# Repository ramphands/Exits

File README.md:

# MOUTH

### ⚠️ THIS MODULE HAS NOT YET BEEN BUILT, ATTEMPT TO BUILD AT YOUR OWN RISK ⚠️

MOUTH is a DIY 8hp eurorack module designed to be the output stage of your patches. It has a 4 channel mixer with individual pan and level controls, and line and headphone outputs.

The project was derived from the [Exits](https://github.com/ramphands/Exits) module. Exits was a combination of the lines mixer project [Nearness](https://github.com/sarnesjo/nearness) and the [Forestcaver headphone amp](https://github.com/forestcaver/Analog-Voice/tree/master/AJH_Headphone_Amp). For MOUTH The patch-based stereo panning of Exits and nearness was changed out for individual pan and level controls for 4 tracks, and the Forestcaver headphone amp (based on the NJM4556AV-TE1 opamp) was changed out for a headphone amp loosely based on Chu Moy's famous ["CMoy" design](https://web.archive.org/web/20021223020724/http://headwize2.powerpill.org/projects/showproj.php?file=cmoy2_prj.htm) - in this case using the RC4580 instead of the OPA134 for availability and experimentation reasons. The module was expanded from 4hp to 8hp to accomodate the extra knobs. I also switched from 1/4" jacks for the two outputs - to 1/8" jacks for everything. The extra space on the widened input board, along with removing the two tall 1/4" jacks, allowed me to flatten the module from two PCBs to just one.

If you'd like to explore the pan + mix section, circuitjs simulation files are in the [simulations](simulations) directory.

The four mixer channels are DC coupled, so you can use this module to mix CV. The headphone output is not DC coupled, so only the line output will output DC offsets. At maximum volume the headphone output is about 1/10 the input level. J5 and J6 are jumpers - no pins bridged means the mixer has a gain of about 1x. Bridging pins 1 and 2 on both jumpers will set the mixer sections gain to 2/3x in case you're mixing hot signals and want to tone things down a bit. To add gain, you could bridge pins 1+2 and then desolder R17 and R20. That'll set the gain to just shy of 2x.

The following sources were used either directly or as learning material to construct the panning and mixing section:

- [Audio Signal Mixing](https://sound-au.com/articles/audio-mixing.htm) By Rod Elliott - a fantastic explainer of mixing circuits
- Erica Synths DIY eurorack [Output and Mixer](https://github.com/erica-synths/diy-eurorack) modules
- [Befaco Hexmix](http://www.befaco.org/hexmix/)

## Schematic and PCBs

-- CURRENTLY OUT OF DATE --

The [kicad](kicad) directory contains the schematic and PCB layout as a KiCad 6 project.

## Panel

-- CURRENTLY OUT OF DATE --

Available in the [panel](panel) directory as a PDF and an SVG vector file.

## Revisions and notes 

- Started with this commit of [Exits](https://github.com/ramphands/Exits/tree/e56ce6f3a76ff6dc0b776ba10d0bfae7fea7ace0)
- Switched from 4hp to 8hp
- Switched from 7 input channels to 4
- Switched from 1/4" jacks for line and hp to 3.5mm / 1/8" jacks for everything.
- Flattened the design from two PCBs to just PCB
- Switched to a CMOY style headphone output using the RC4580
- MOUTH's first "complete" post-Exits scheamtic, using passive mixing can be found in the git history [here](https://github.com/coryalder/Exits/blob/65a9d2693df2f5ae9116ffd591f22e5cf609d3db/exits%20schematic.april12th.pdf). After that I switched to current based mixing, per Rod Elliott's article
- MOUTH's first "complete" + "current-based" schematic is [here](https://github.com/coryalder/Exits/tree/e56ce6f3a76ff6dc0b776ba10d0bfae7fea7ace0)
- Re-routed the board with the changes above

## Todos:

- Make a panel and panel template
- Add 3d models for all the parts used
- Add board rendering images to the readme
- Add test points to make debugging easier
- Build one, and confirm all of this works as intended

## License

[CC BY-SA 4.0](http://creativecommons.org/licenses/by-sa/4.0/)

To summarize the license linked above - you are free to:

* Share — copy and redistribute the material in any medium or format
* Adapt — remix, transform, and build upon the material
for any purpose, even commercially. 

As long as you abide by the terms of the license which requires:

* Attribution — You must give appropriate credit, provide a link to the license, and indicate if changes were made. You may do so in any reasonable manner, but not in any way that suggests the licensor endorses you or your use.

* ShareAlike — If you remix, transform, or build upon the material, you must distribute your contributions under the same license as the original.

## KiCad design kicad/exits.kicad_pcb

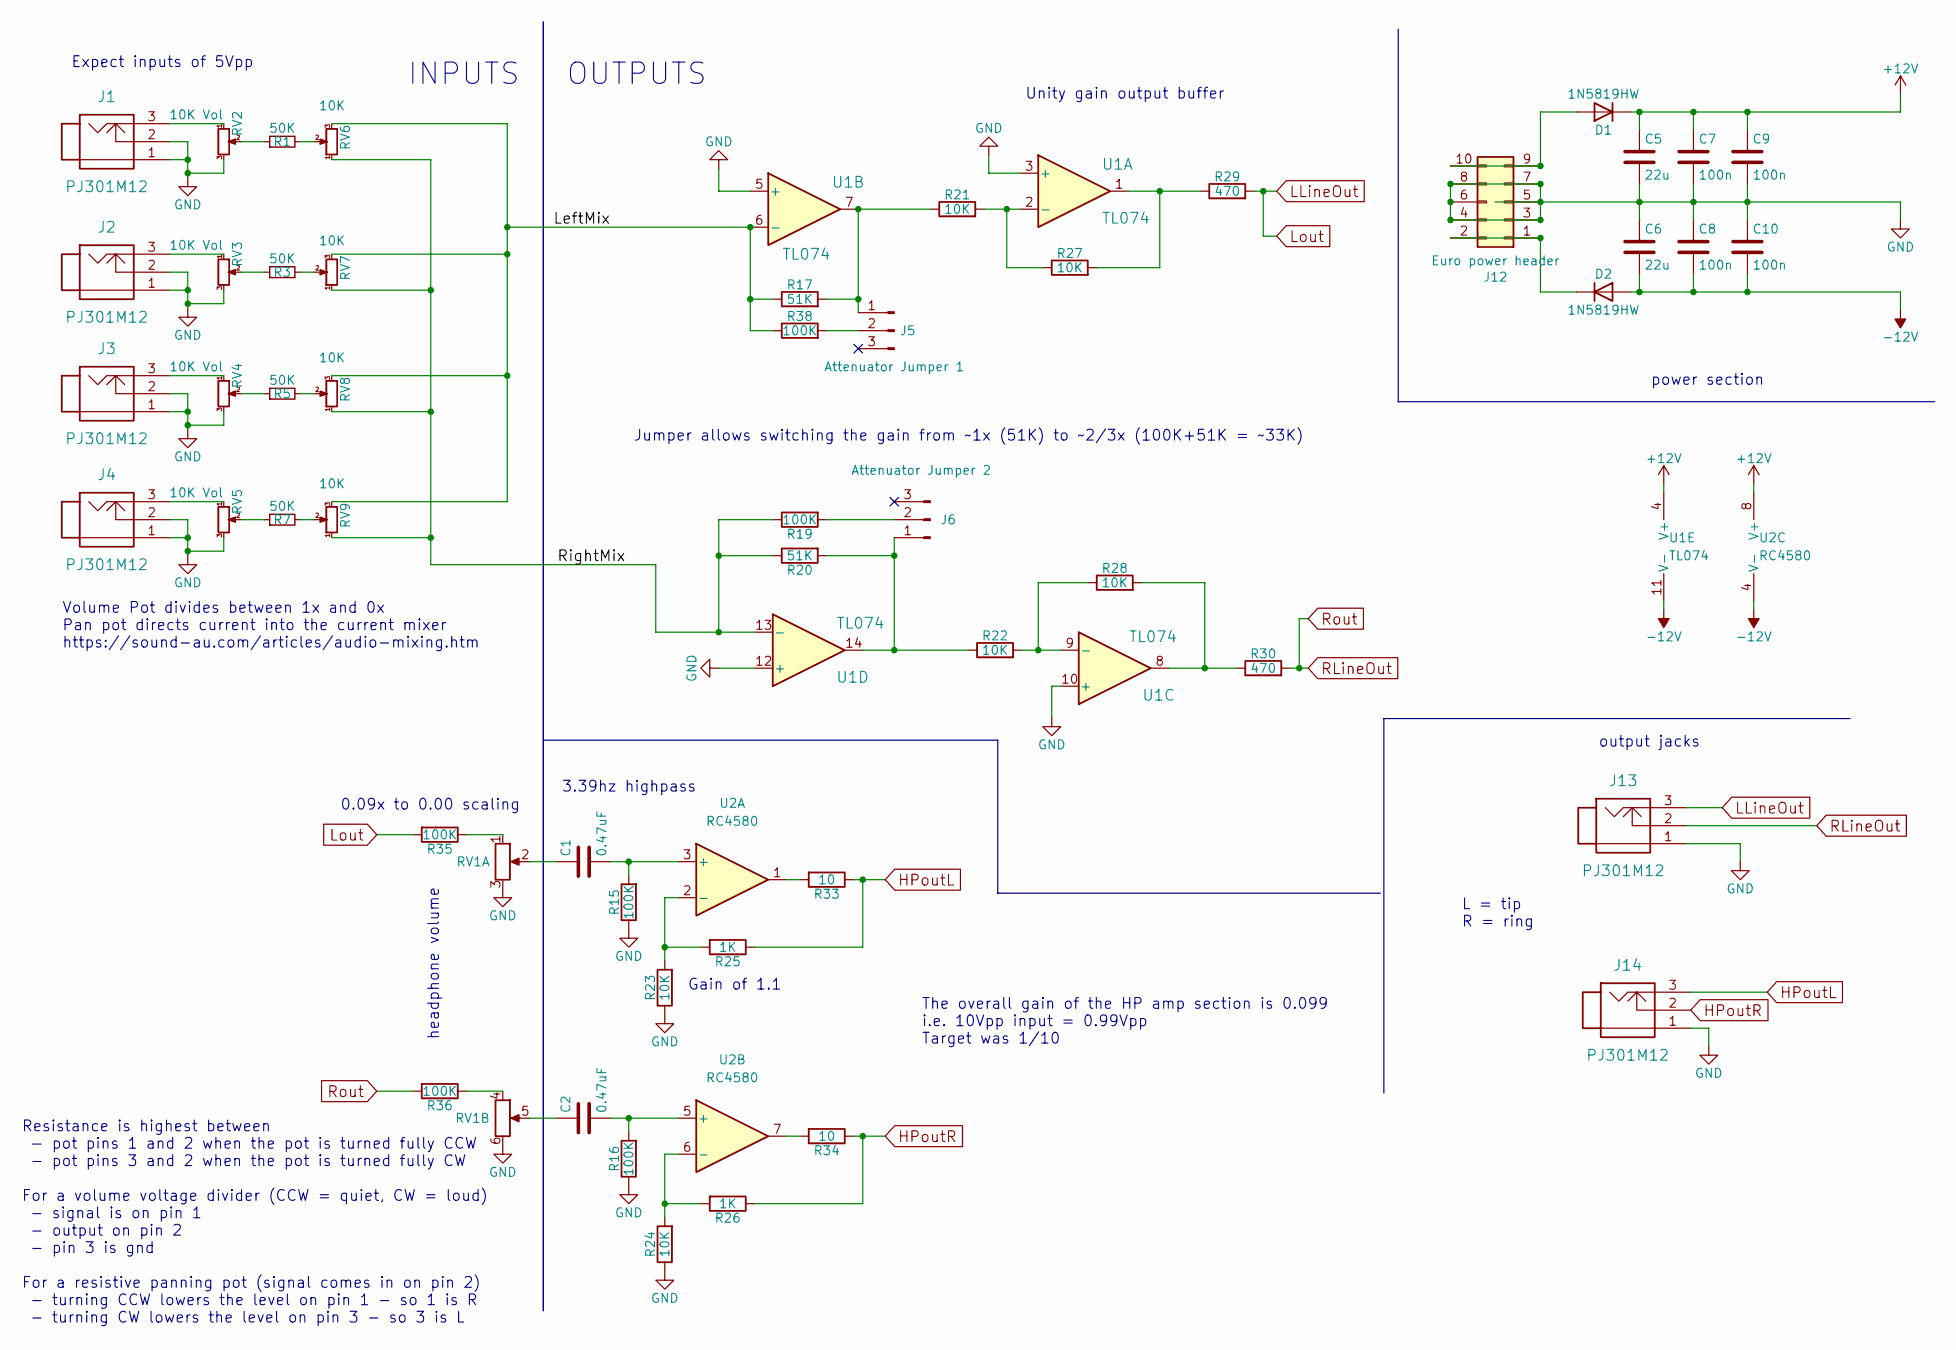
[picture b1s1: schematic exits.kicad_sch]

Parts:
C1, C2: 0.47uF; C_1206_3216Metric
C5, C6: 22u; C_0805_2012Metric
C7, C8, C9, C10: 100n; C_0603_1608Metric
D1, D2: 1N5819HW; SOD-123
J1, J2, J3, J4, J13, J14: PJ301M12
J5: Attenuator Jumper 1; PinHeader_1x03_P2.54mm_Vertical
J6: Attenuator Jumper 2; PinHeader_1x03_P2.54mm_Vertical
J12: Euro power header; IDC-Header_2x05_P2.54mm_Vertical
R1, R3, R5, R7: 50K; R_0603_1608Metric
R15, R16, R35, R36: 100K; R_0805_2012Metric
R17, R20: 51K; R_0603_1608Metric
R19, R38: 100K; R_0603_1608Metric
R21, R22, R27, R28: 10K; R_0603_1608Metric
R23, R24: 10K; R_0805_2012Metric
R25, R26: 1K; R_0805_2012Metric
R29, R30: 470; R_0603_1608Metric
R33, R34: 10; R_1206_3216Metric
RV1: B10K; Potentiometer_Alpha_RD902F-40-00D_Dual_Vertical
RV2, RV3, RV4, RV5: 10K Vol; Potentiometer_Alps_RK09K_Single_Vertical
RV6, RV7, RV8, RV9: 10K; Potentiometer_Alps_RK09K_Single_Vertical
U1: TL074; SOIC-14_3.9x8.7mm_P1.27mm
U2: RC4580; SOIC-8_3.9x4.9mm_P1.27mm

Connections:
+12V: C5.1, C7.1, C9.1, D1.1 (K), U1.4 (V+), U2.8 (V+)
-12V: C6.2, C8.2, C10.2, D2.2 (A), U1.11 (V-), U2.4 (V-)
/LeftMix: R17.1, R38.1, RV6.3, RV7.3, RV8.3, RV9.3, U1.6 (-)
/RightMix: R19.1, R20.1, RV6.1, RV7.1, RV8.1, RV9.1, U1.13 (-)
GND: C5.2, C6.1, C7.2, C8.1, C9.2, C10.1, J1.1, J1.2, J2.1, J2.2, J3.1, J3.2, J4.1, J4.2, J12.3, J12.4, J12.5, J12.6, J12.7, J12.8, J13.1, J14.1, R15.1, R16.1, R23.1, R24.1, RV1.3, RV1.6, RV2.3, RV3.3, RV4.3, RV5.3, U1.3 (+), U1.5 (+), U1.10 (+), U1.12 (+)
HPoutL: J14.3, R25.1, R33.1
HPoutR: J14.2, R26.1, R34.1
LLineOut: J13.3, R29.2, R35.2
unnamed: C1.1, RV1.2
unnamed: C1.2, R15.2, U2.3 (+)
unnamed: C2.1, RV1.5
unnamed: C2.2, R16.2, U2.5 (+)
unnamed: D1.2 (A), J12.9, J12.10
unnamed: D2.1 (K), J12.1, J12.2
unnamed: J1.3, RV2.1
unnamed: J2.3, RV3.1
unnamed: J3.3, RV4.1
unnamed: J4.3, RV5.1
unnamed: J5.1, R17.2, R21.1, U1.7
unnamed: J5.2, R38.2
unnamed: J6.1, R20.2, R22.1, U1.14
unnamed: J6.2, R19.2
unnamed: R1.1, RV2.2
unnamed: R1.2, RV6.2
unnamed: R3.1, RV3.2
unnamed: R3.2, RV7.2
unnamed: R5.1, RV4.2
unnamed: R5.2, RV8.2
unnamed: R7.1, RV5.2
unnamed: R7.2, RV9.2
unnamed: R21.2, R27.1, U1.2 (-)
unnamed: R22.2, R28.1, U1.9 (-)
unnamed: R23.2, R25.2, U2.2 (-)
unnamed: R24.2, R26.2, U2.6 (-)
unnamed: R27.2, R29.1, U1.1
unnamed: R28.2, R30.1, U1.8
unnamed: R33.2, U2.1
unnamed: R34.2, U2.7
unnamed: R35.1, RV1.1
unnamed: R36.1, RV1.4
RLineOut: J13.2, R30.2, R36.2

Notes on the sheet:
The overall gain of the HP amp section is 0.099 i.e. 10Vpp input = 0.99Vpp Target was 1/10
headphone volume
3.39hz highpass
INPUTS
Volume Pot divides between 1x and 0x Pan pot directs current into the current mixer https://sound-au.com/articles/audio-mixing.htm
L = tip R = ring
Unity gain output buffer
0.09x to 0.00 scaling
Gain of 1.1
OUTPUTS
Jumper allows switching the gain from ~1x (51K) to ~2/3x (100K+51K = ~33K)
output jacks
Expect inputs of 5Vpp
power section
Resistance is highest between - pot pins 1 and 2 when the pot is turned fully CCW - pot pins 3 and 2 when the pot is turned fully CW For a volume voltage divider (CCW = quiet, CW = loud) - signal is on pin 1 - output on pin 2 - pin 3 is gnd For a resistive panning pot (signal comes in on pin 2) - t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

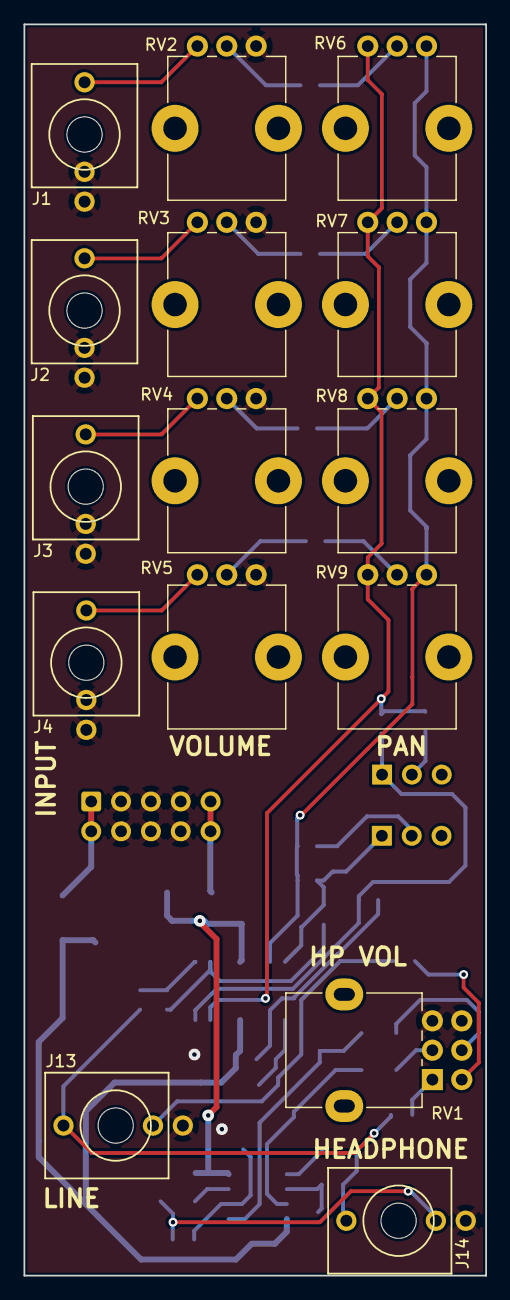
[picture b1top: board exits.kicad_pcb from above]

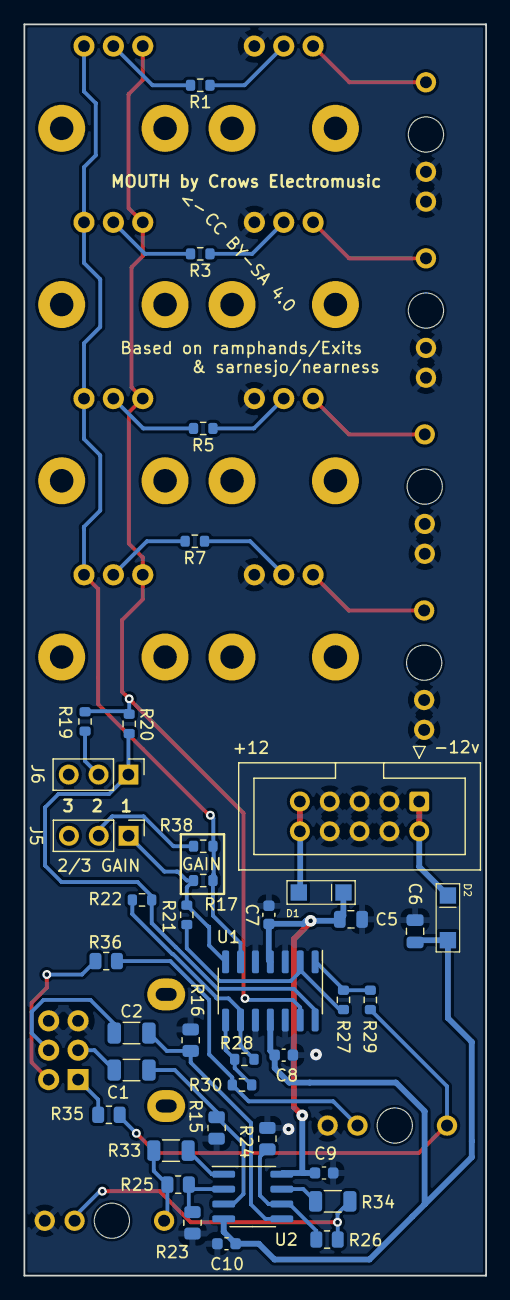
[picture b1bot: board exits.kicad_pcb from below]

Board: 2 copper layers, 39.3 x 106.5 mm, 54 parts (39 on the bottom side), 41 nets.

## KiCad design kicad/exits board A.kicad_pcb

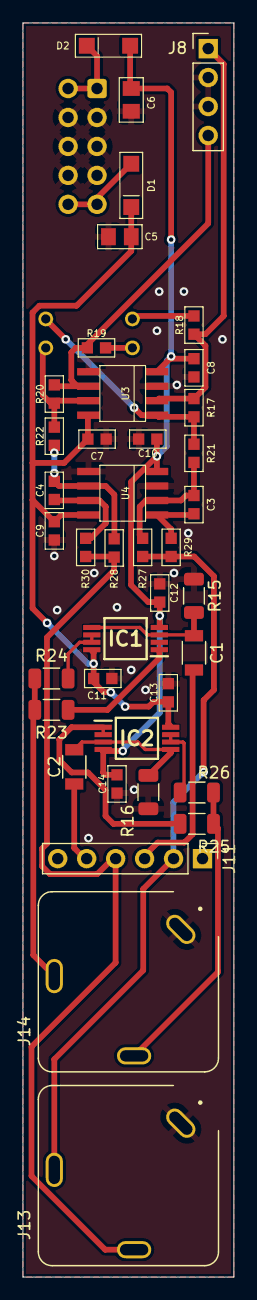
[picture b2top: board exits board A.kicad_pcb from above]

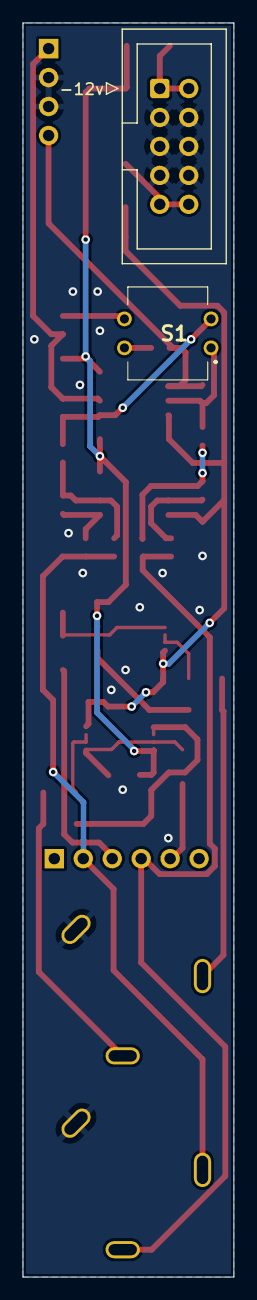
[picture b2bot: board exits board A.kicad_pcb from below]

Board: 2 copper layers, 18.5 x 110.0 mm, 42 parts (2 on the bottom side), 27 nets.

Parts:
C1, C2: 100n; C_1206
C3, C4: 22p; 0603
C5, C6: 22u; 0805
C7, C8, C9, C10, C11, C12, C13, C14: 100n; 0603
D1, D2: 1N5819HW; SOD-123
IC1, IC2: NJM4556AV-TE1; SOP65P640X145-8N
J8: Conn_01x03_Male; PinHeader_1x04_P2.54mm_Vertical
J11: Conn_01x04_Male; PinHeader_1x06_P2.54mm_Vertical
J12: Conn_02x05_Odd_Even; IDC-Header_2x05_P2.54mm_Vertical
J13, J14: SJ-63083A; CUI_SJ-63083A
R15, R16: 100k; R_1206_3216Metric
R17, R18, R19, R20, R21, R22, R27, R28: 100k; 0603
R23, R24, R25, R26: 1; R_1206_3216Metric
R29, R30: 1k; 0603
S1: ADP0204
U3, U4: LME49720; SOIC-8

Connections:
+12V: C5.1, C7.1, C9.1, C11.1, C13.1, D1.1 (K), IC1.8 (V+), IC2.8 (V+), U3.8, U4.8
-12V: C6.2, C8.2, C10.2, C12.2, C14.2, D2.2 (A), IC1.4 (V-), IC2.4 (V-), U3.4, U4.4
GND: C5.2, C6.1, C7.2, C8.1, C9.2, C10.1, C11.2, C12.1, C13.2, C14.1, J8.2, J8.3, J12.3, J12.4, J12.5, J12.6, J12.7, J12.8, J13.1, J14.1, R15.1, R16.1, U3.3 (+), U3.5 (+), U4.3 (+), U4.5 (+)
HPoutL: J14.4, R23.2, R24.2
HPoutR: J14.3, R25.2, R26.2
Lout: J11.2, J13.4, R27.2, R29.2
unnamed: C1.1, J11.3
unnamed: C1.2, IC1.3 (A_+INPUT), IC1.5 (B_+INPUT), R15.2
unnamed: C2.1, J11.5
unnamed: C2.2, IC2.3 (A_+INPUT), IC2.5 (B_+INPUT), R16.2
unnamed: C3.1, R21.2, R27.1, U4.2 (-)
unnamed: C3.2, R29.1, U4.1
unnamed: C4.1, R22.2, R28.1, U4.6 (-)
unnamed: C4.2, R30.1, U4.7
unnamed: D1.2 (A), J12.9, J12.10
unnamed: D2.1 (K), J12.1, J12.2
unnamed: IC1.1 (A_OUTPUT), IC1.2 (A_-INPUT), R23.1
unnamed: IC1.6 (B_-INPUT), IC1.7 (B_OUTPUT), R24.1
unnamed: IC2.1 (A_OUTPUT), IC2.2 (A_-INPUT), R25.1
unnamed: IC2.6 (B_-INPUT), IC2.7 (B_OUTPUT), R26.1
unnamed: J8.1, R17.1, R18.1, U3.2 (-)
unnamed: J8.4, R19.1, R20.1, U3.6 (-)
unnamed: R17.2, R21.1, S1.A2, U3.1
unnamed: R18.2, S1.B2
unnamed: R19.2, S1.B1
unnamed: R20.2, R22.1, S1.A1, U3.7
Rout: J11.4, J13.3, R28.2, R30.2

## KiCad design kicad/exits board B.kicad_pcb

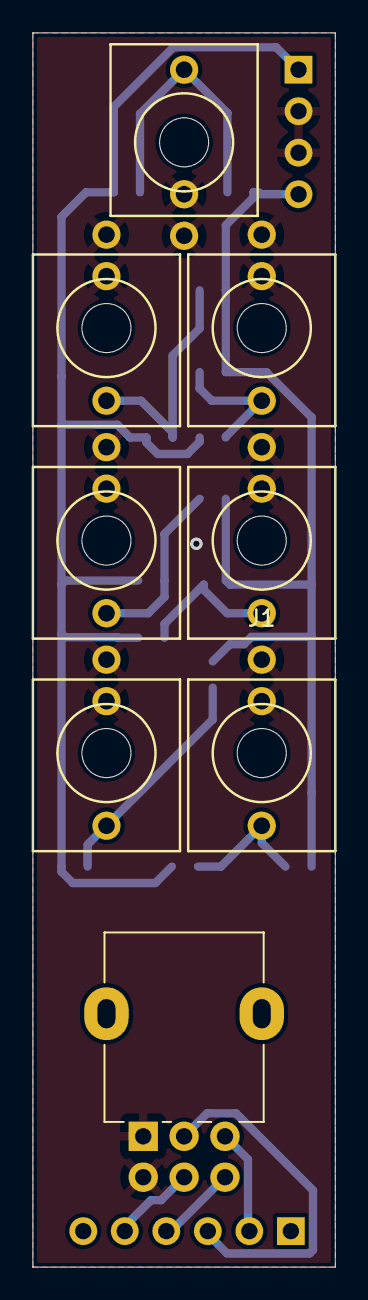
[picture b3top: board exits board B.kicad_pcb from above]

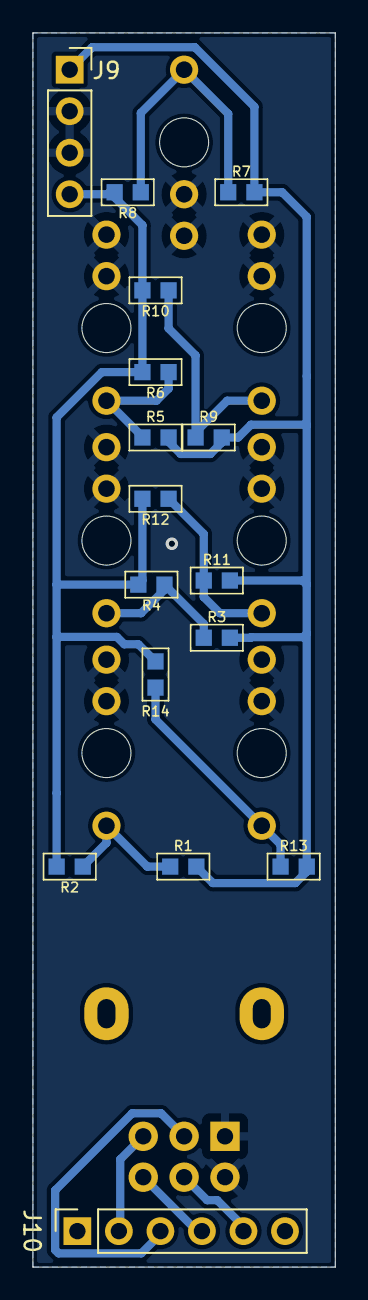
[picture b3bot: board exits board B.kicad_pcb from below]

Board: 2 copper layers, 18.5 x 75.5 mm, 24 parts (16 on the bottom side), 14 nets.

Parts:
J1, J2, J3, J4, J5, J6, J7: PJ301M12
J9: Conn_01x03_Female; PinSocket_1x04_P2.54mm_Vertical
J10: Conn_01x04_Female; PinSocket_1x06_P2.54mm_Vertical
R1, R14: 100k; 0603
R2, R13: 1M67; 0603
R3, R12: 103k; 0603
R4, R11: 439k; 0603
R5, R10: 113k; 0603
R6, R9: 215k; 0603
R7, R8: 141k; 0603
RV1: R_POT_Dual_Separate; Potentiometer_Alpha_RD902F-40-00D_Dual_Vertical

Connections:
GND: J1.1, J1.2, J2.1, J2.2, J3.1, J3.2, J4.1, J4.2, J5.1, J5.2, J6.1, J6.2, J7.1, J7.2, J9.2, J9.3, RV1.1, RV1.4
unnamed: J1.3, R1.1, R2.1
unnamed: J2.3, R3.1, R4.1
unnamed: J3.3, R5.1, R6.1
unnamed: J4.3, R7.1, R8.1
unnamed: J5.3, R9.1, R10.1
unnamed: J6.3, R11.1, R12.1
unnamed: J7.3, R13.1, R14.1
unnamed: J9.1, R1.2, R3.2, R5.2, R7.2, R9.2, R11.2, R13.2
unnamed: J9.4, R2.2, R4.2, R6.2, R8.2, R10.2, R12.2, R14.2
unnamed: J10.2, RV1.3
unnamed: J10.3, RV1.2
unnamed: J10.4, RV1.6
unnamed: J10.5, RV1.5

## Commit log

2022-01-27 Add files via upload
    Contains schematics, PCB designs, associated footprints and symbols.
    Also contains gerbers for the two boards in the subfolder.
2022-01-27 Add files via upload
    prototype version
2022-01-27 Add files via upload
    image of the original prototype
2022-01-30 Add files via upload
    Contains BOM as a .ODS file (with Mouser links) and an interactive BOM (iBOM)
2022-04-10 Switched to CMOY style hp out w RC4850, and added stereo panning
2022-04-11 add panel outline, tweak R values, dips -> headers
2022-04-12 Switched to non-inverting amp config, tweaked values
2022-04-12 add schematic pdf
2022-04-14 Switched to current mixing, updated pcb
2022-04-19 added my readme
2022-04-19 updated readme again
2022-04-20 Switched L and R channels, so pots all turn the right way
2022-04-20 update schematic
2022-04-20 removed old schematic
